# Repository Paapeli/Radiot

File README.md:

# Radiot
Pot->ppm RC radio transmitter

More information maybe coming later. Use at your own risk, the author takes no responsibility whatsoever of the functionality.

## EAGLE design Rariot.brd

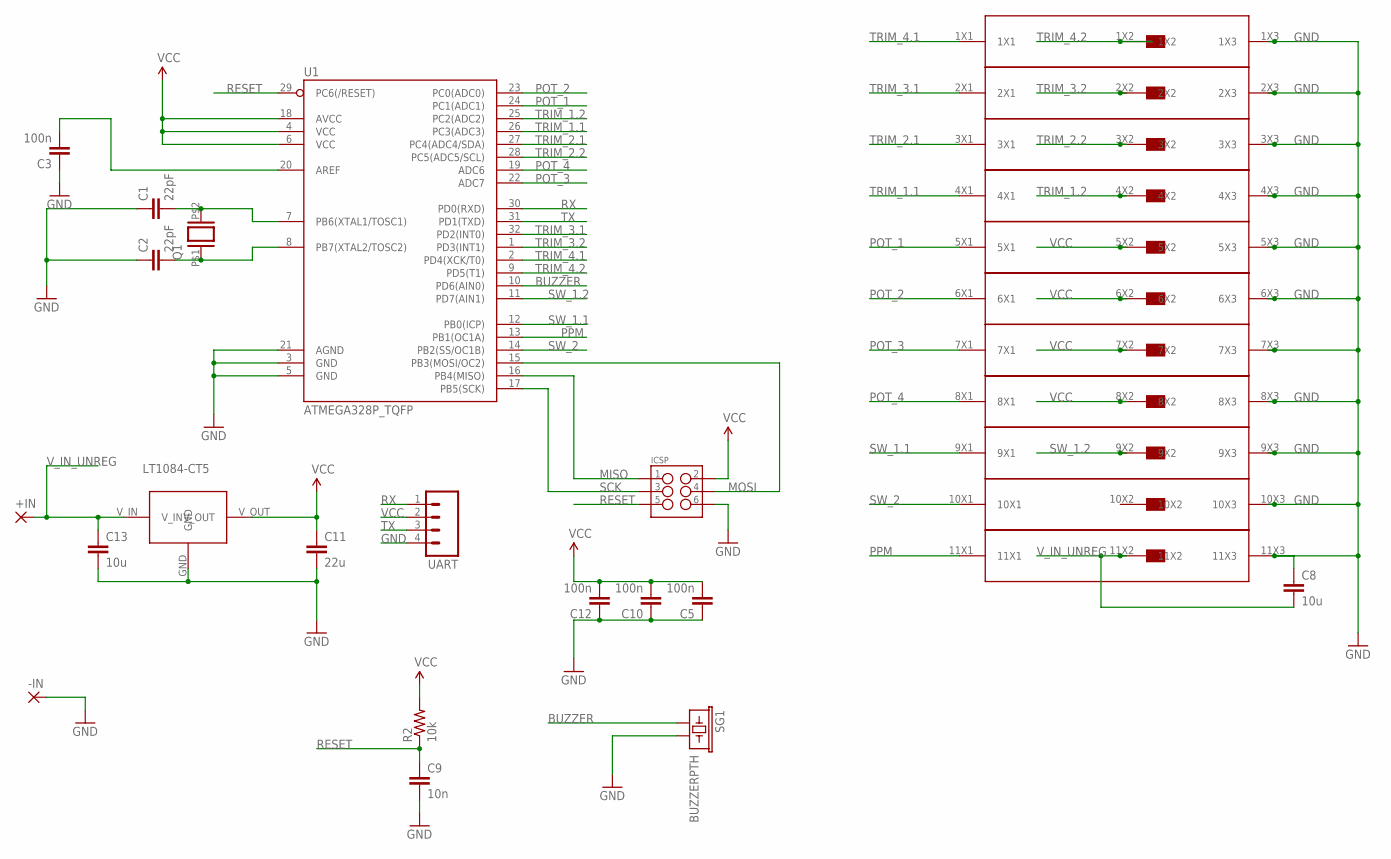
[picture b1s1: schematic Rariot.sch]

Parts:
+IN: SMD5; SMD2,54-5,08
-IN: SMD5; SMD2,54-5,08
C1, C2: 22pF; 0805
C3, C5, C10, C12: 100n; 0805
C8, C13: 10u; 1206
C9: 10n; 0805
C11: 22u; 1206
ICSP: FEMALE 2x3; 2X3
Q1: XTAL/SSMD; X-TAL_SMD
R2: 10k; 0805
SG1: BUZZERPTH; BUZZER-12MM
U1: ATMEGA328P_TQFP; TQFP32-08
U$1: 11X3_2.54_PIN_HEADER; 11X3_2,54_PIN_HEADER
U$2: LT1084-CT5; TO-220
UART: M04PTH; 1X04

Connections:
BUZZER: SG1.+ (1), U1.10 (PD6(AIN0))
GND: -IN.1, C1.1, C2.1, C3.1, C5.1, C8.1, C9.2, C10.1, C11.2, C12.1, C13.2, ICSP.6, SG1.- (2), U1.3 (GND), U1.5 (GND), U1.21 (AGND), U$1.1X3, U$1.2X3, U$1.3X3, U$1.4X3, U$1.5X3, U$1.6X3, U$1.7X3, U$1.8X3, U$1.9X3, U$1.10X3, U$1.11X3, U$2.GND, UART.4
MISO: ICSP.1, U1.16 (PB4(MISO))
MOSI: ICSP.4, U1.15 (PB3(MOSI/OC2))
unnamed: C1.2, Q1.P$2 (2), U1.7 (PB6(XTAL1/TOSC1))
unnamed: C3.2, U1.20 (AREF)
unnamed: C2.2, Q1.P$1 (1), U1.8 (PB7(XTAL2/TOSC2))
POT_1: U1.24 (PC1(ADC1)), U$1.5X1
POT_2: U1.23 (PC0(ADC0)), U$1.6X1
POT_3: U1.22 (ADC7), U$1.7X1
POT_4: U1.19 (ADC6), U$1.8X1
PPM: U1.13 (PB1(OC1A)), U$1.11X1
RESET: C9.1, ICSP.5, R2.1, U1.29 (PC6(/RESET))
RX: U1.30 (PD0(RXD)), UART.1
SCK: ICSP.3, U1.17 (PB5(SCK))
SW_1.1: U1.12 (PB0(ICP)), U$1.9X1
SW_1.2: U1.11 (PD7(AIN1)), U$1.9X2
SW_2: U1.14 (PB2(SS/OC1B)), U$1.10X1
TRIM_1.1: U1.26 (PC3(ADC3)), U$1.4X1
TRIM_1.2: U1.25 (PC2(ADC2)), U$1.4X2
TRIM_2.1: U1.27 (PC4(ADC4/SDA)), U$1.3X1
TRIM_2.2: U1.28 (PC5(ADC5/SCL)), U$1.3X2
TRIM_3.1: U1.32 (PD2(INT0)), U$1.2X1
TRIM_3.2: U1.1 (PD3(INT1)), U$1.2X2
TRIM_4.1: U1.2 (PD4(XCK/T0)), U$1.1X1
TRIM_4.2: U1.9 (PD5(T1)), U$1.1X2
TX: U1.31 (PD1(TXD)), UART.3
VCC: C5.2, C10.2, C11.1, C12.2, ICSP.2, R2.2, U1.4 (VCC), U1.6 (VCC), U1.18 (AVCC), U$1.5X2, U$1.6X2, U$1.7X2, U$1.8X2, U$2.V_OUT, UART.2
V_IN_UNREG: +IN.1, C8.2, C13.1, U$1.11X2, U$2.V_IN

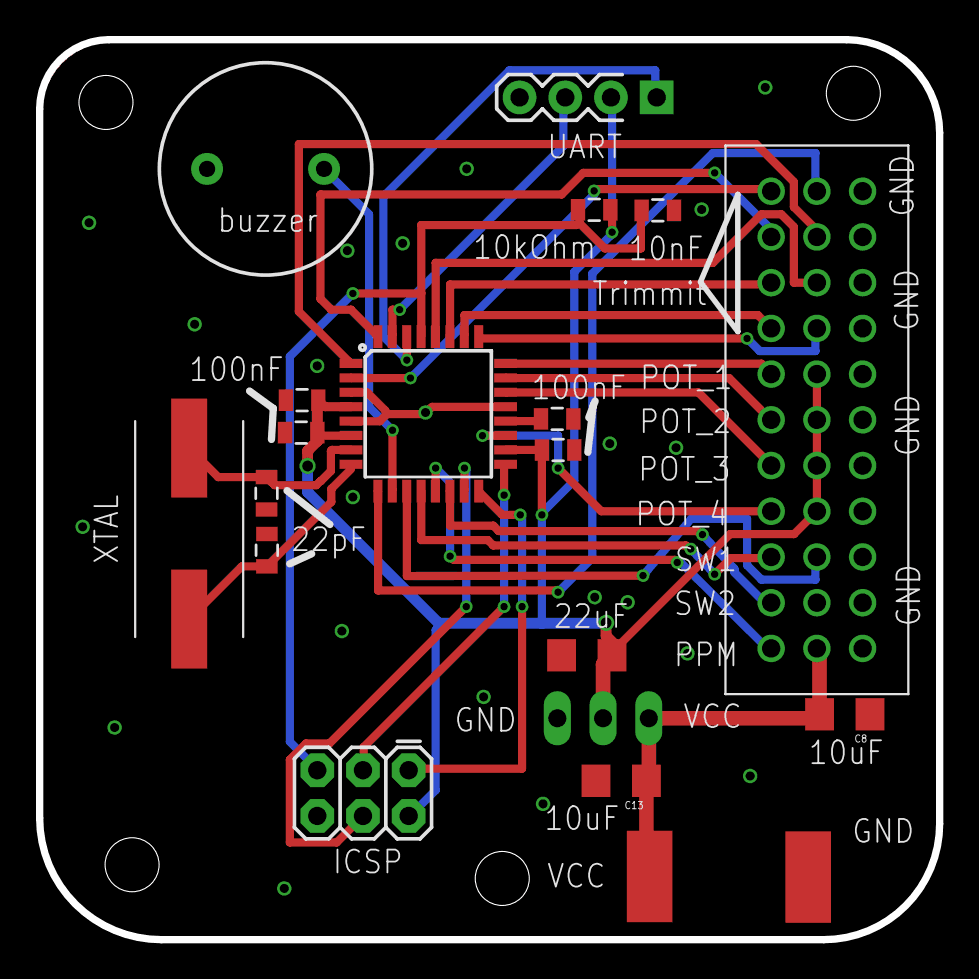
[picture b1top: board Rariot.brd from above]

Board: 2 copper layers, 50.0 x 50.0 mm, 20 parts (0 on the bottom side), 29 nets.

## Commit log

2017-01-30 Add files via upload
    Radiopiirilevyn elektroniikkaosio

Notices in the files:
parts and their libraries:
SparkFun-Capacitors: Licensing: Creative Commons ShareAlike 4.0 International - https://creativecommons.org/licenses/by-sa/4.0
